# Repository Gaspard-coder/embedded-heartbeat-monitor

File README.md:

# This repository contains all of the necessary file to make a working heartbeat sensor
- Schematics
- PCB design files
- Embedded code running on MCUs

## Embedded software (`software/hsensor/`)

MicroPython application running on a Raspberry Pi Pico. It samples the
output of the TCRT5000 reflectance sensor (amplified by an op-amp), detects
heartbeats and displays the BPM together with the live waveform on the
0.96" ST7735 LCD.

### Files
- `ST7735.py` — driver for the 0.96" LCD (SPI, same wiring as the demo:
  DC=GP8, CS=GP9, SCK=GP10, MOSI=GP11, RST=GP12, BL=GP13).
- `main.py` — acquisition, heart rate detection and display loop.

### Wiring
- TCRT5000 + op-amp output → **pin 31 (GPIO26 / ADC0)** of the Pico.
- LCD: SPI1 on GP8–GP13 (see above).

### How the algorithm works

1. **Sampling.** `ADC(Pin(26))` is read every 10 ms (≈100 Hz), which is
   well above the highest expected heart-beat frequency (~3 Hz at 180 BPM)
   and matches the cutoff of the analog front-end.

2. **DC removal (high-pass filter).** The raw photoplethysmographic signal
   coming from the TCRT5000 is dominated by a large DC component (ambient
   reflectance of the skin) with a small pulsatile AC component on top. We
   subtract a slowly-tracking baseline computed as an exponential moving
   average:

   ```
   baseline ← (31 · baseline + raw) / 32
   x       ← raw − baseline
   ```

   With `α = 1/32` at 100 Hz, the equivalent cutoff is roughly 0.5 Hz —
   slow enough to leave the heartbeats untouched but fast enough to track
   drift in finger pressure or ambient light.

3. **Peak detection.** A heartbeat appears as a local maximum on the
   filtered signal `x`. For every new sample we check the *previous*
   sample: if it is greater than its two neighbours and above
   `PEAK_THRESHOLD`, it is declared a peak.

4. **Refractory period.** Once a peak has been detected, any new peak
   occurring within 300 ms is ignored. This caps the detected rate at
   200 BPM and avoids counting the dicrotic notch (the small secondary
   bump after each beat) as a separate heartbeat.

5. **BPM computation.** The time difference `dt` between two consecutive
   accepted peaks is pushed into a rolling buffer of the last 5
   intervals. The current heart rate is the average of that buffer:

   ```
   BPM = 60000 / mean(intervals_ms)
   ```

   Averaging over several beats smooths jitter due to noise and gives a
   stable reading on the display. If no peak is seen for more than 2 s
   (i.e. < 30 BPM, almost certainly a lost-contact event) the buffer is
   cleared and the BPM goes back to `--`.

6. **Display.** The LCD is refreshed every 200 ms — redrawing the full
   framebuffer is slow, so we deliberately do not refresh at the sampling
   rate. The top of the screen shows `BPM: XX`, and below it the last
   160 filtered samples are plotted (oldest on the left, newest on the
   right) with a blue zero-line.

### Tuning knobs (top of `main.py`)
- `PEAK_THRESHOLD` — minimum amplitude (in ADC LSB on the filtered signal)
  for a sample to qualify as a peak. Lower it if the analog gain is small,
  raise it if the signal is noisy.
- `BPM_WINDOW` — number of inter-beat intervals averaged.
- `REFRACTORY_MS` / `MAX_INTERVAL_MS` — accepted BPM range (currently
  30–200 BPM).
- `v // 30` in the plotting code — vertical scale of the waveform on the
  LCD.

### Running
Copy `ST7735.py` and `main.py` to the Pico (Thonny, `mpremote cp`, …).
`main.py` runs automatically at boot.

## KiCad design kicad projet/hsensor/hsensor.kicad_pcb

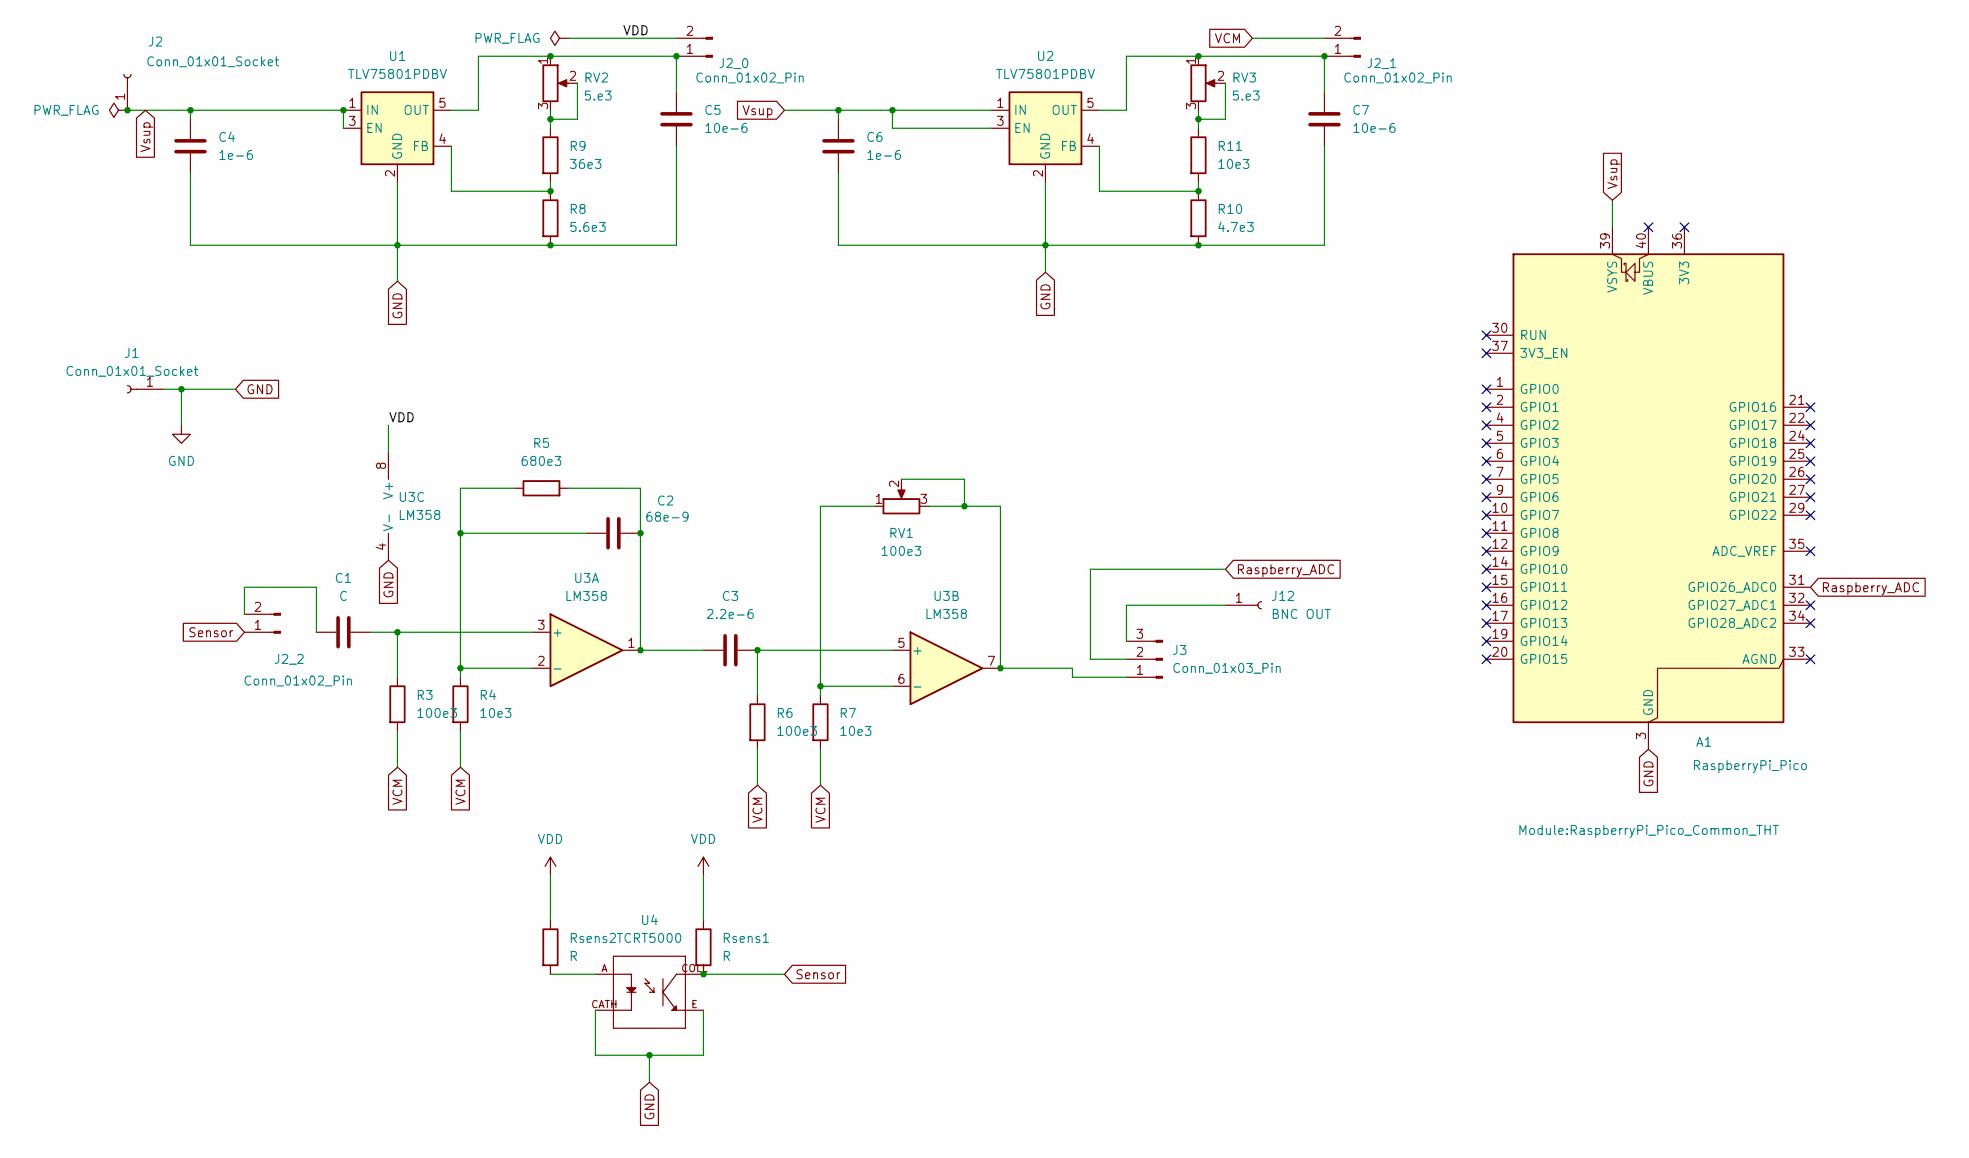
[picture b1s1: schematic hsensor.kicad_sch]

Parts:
A1: RaspberryPi_Pico; RaspberryPi_Pico_Common_THT
C1: C; C_1206_3216Metric
C2: 68e-9; C_1206_3216Metric
C3: 2.2e-6; C_1206_3216Metric
C4, C6: 1e-6; C_1206_3216Metric
C5, C7: 10e-6; C_1206_3216Metric
J1, J2: Conn_01x01_Socket
J2_0, J2_1, J2_2: Conn_01x02_Pin; PinHeader_1x02_P2.54mm_Vertical
J3: Conn_01x03_Pin; PinHeader_1x03_P2.54mm_Vertical
J12: BNC OUT
R3, R6: 100e3; R_1206_3216Metric
R4, R7, R11: 10e3; R_1206_3216Metric
R5: 680e3; R_1206_3216Metric
R8: 5.6e3; R_1206_3216Metric
R9: 36e3; R_1206_3216Metric
R10: 4.7e3; R_1206_3216Metric
RV1: 100e3; Potentiometer_Bourns_3266Y_Vertical
RV2, RV3: 5.e3; Potentiometer_Bourns_3266Y_Vertical
Rsens1, Rsens2: R; R_1206_3216Metric
U1, U2: TLV75801PDBV; SOT-23-5
U3: LM358; DIP-8_W7.62mm_Socket
U4: TCRT5000; OPTO_TCRT5000; PARTREV 1.7

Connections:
GND: A1.3 (GND), A1.8 (GND), A1.13 (GND), A1.18 (GND), A1.23 (GND), A1.28 (GND), A1.38 (GND), C4.1, C5.1, C6.1, C7.1, J1.1, R8.2, R10.2, U1.2 (GND), U2.2 (GND), U3.4 (V-), U4.CATH, U4.E
unnamed: C2.1, C3.2, R5.2, U3.1
unnamed: C5.2, J2_0.1, RV2.1, U1.5 (OUT)
unnamed: C7.2, J2_1.1, RV3.1, U2.5 (OUT)
unnamed: C1.2, J2_2.2
unnamed: J3.1, RV1.2, RV1.3, U3.7
unnamed: J3.3, J12.1
unnamed: R9.1, RV2.2, RV2.3
unnamed: R11.1, RV3.2, RV3.3
unnamed: Rsens2.2, U4.A
unnamed: R8.1, R9.2, U1.4 (FB)
unnamed: R10.1, R11.2, U2.4 (FB)
unnamed: C1.1, R3.1, U3.3 (+)
unnamed: C2.2, R4.1, R5.1, U3.2 (-)
unnamed: C3.1, R6.1, U3.5 (+)
unnamed: R7.1, RV1.1, U3.6 (-)
Raspberry_ADC: A1.31 (GPIO26_ADC0), J3.2
Sensor: J2_2.1, Rsens1.2, U4.COLL
VCM: J2_1.2, R3.2, R4.2, R6.2, R7.2
VDD: J2_0.2, Rsens1.1, Rsens2.1, U3.8 (V+)
Vsup: A1.39 (VSYS), C4.2, C6.2, J2.1, U1.1 (IN), U1.3 (EN), U2.1 (IN), U2.3 (EN)

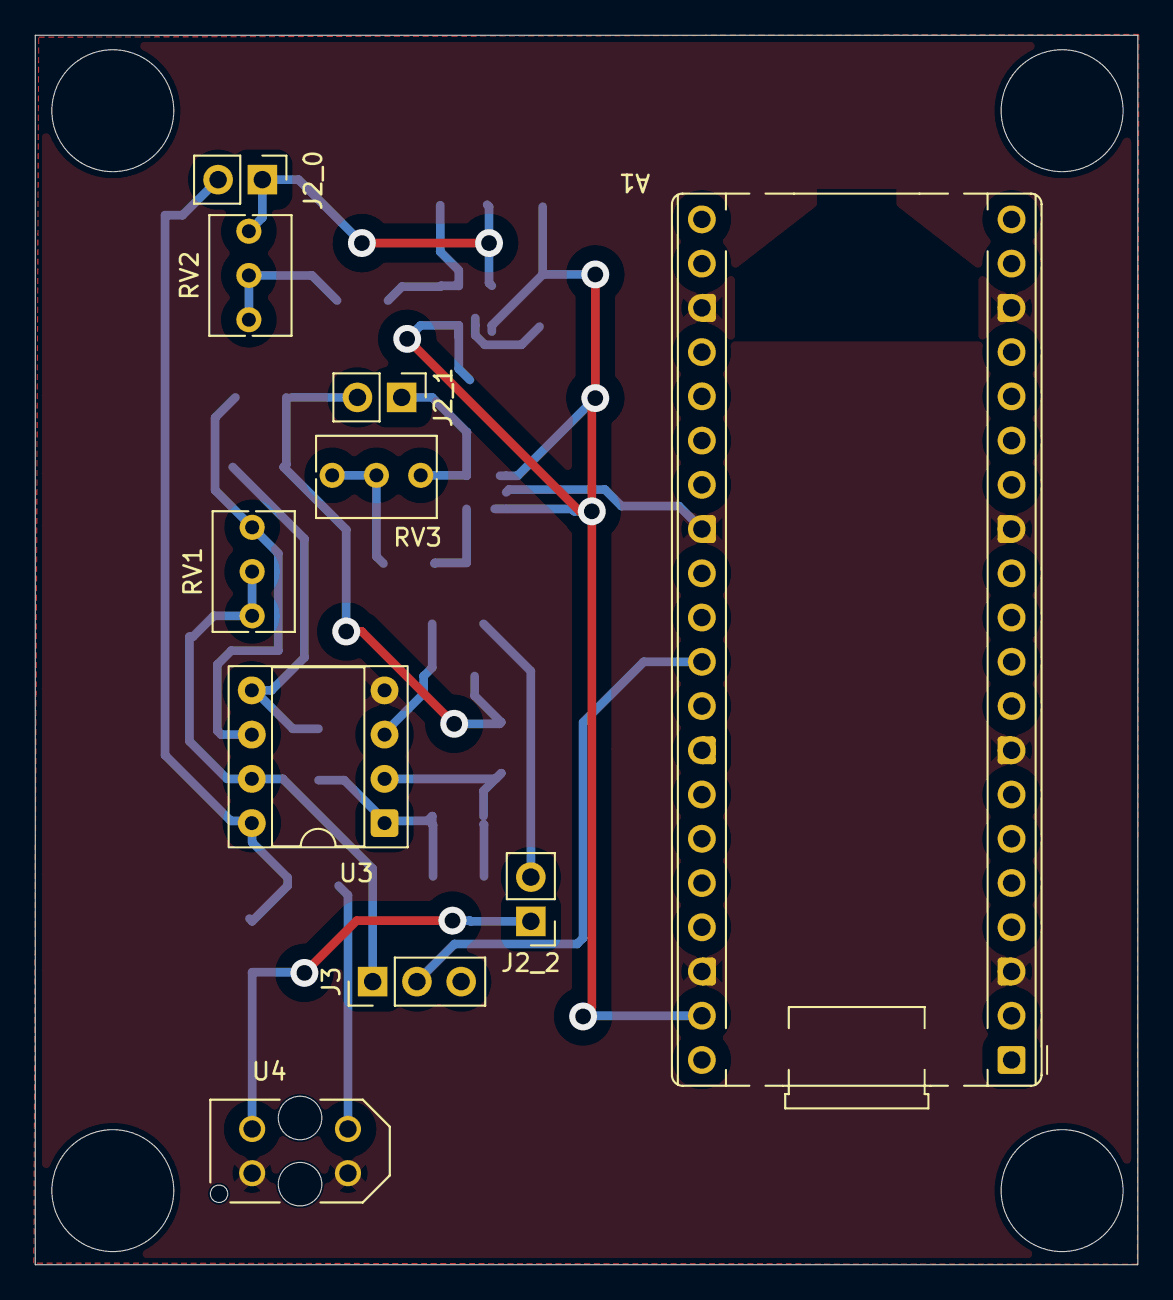
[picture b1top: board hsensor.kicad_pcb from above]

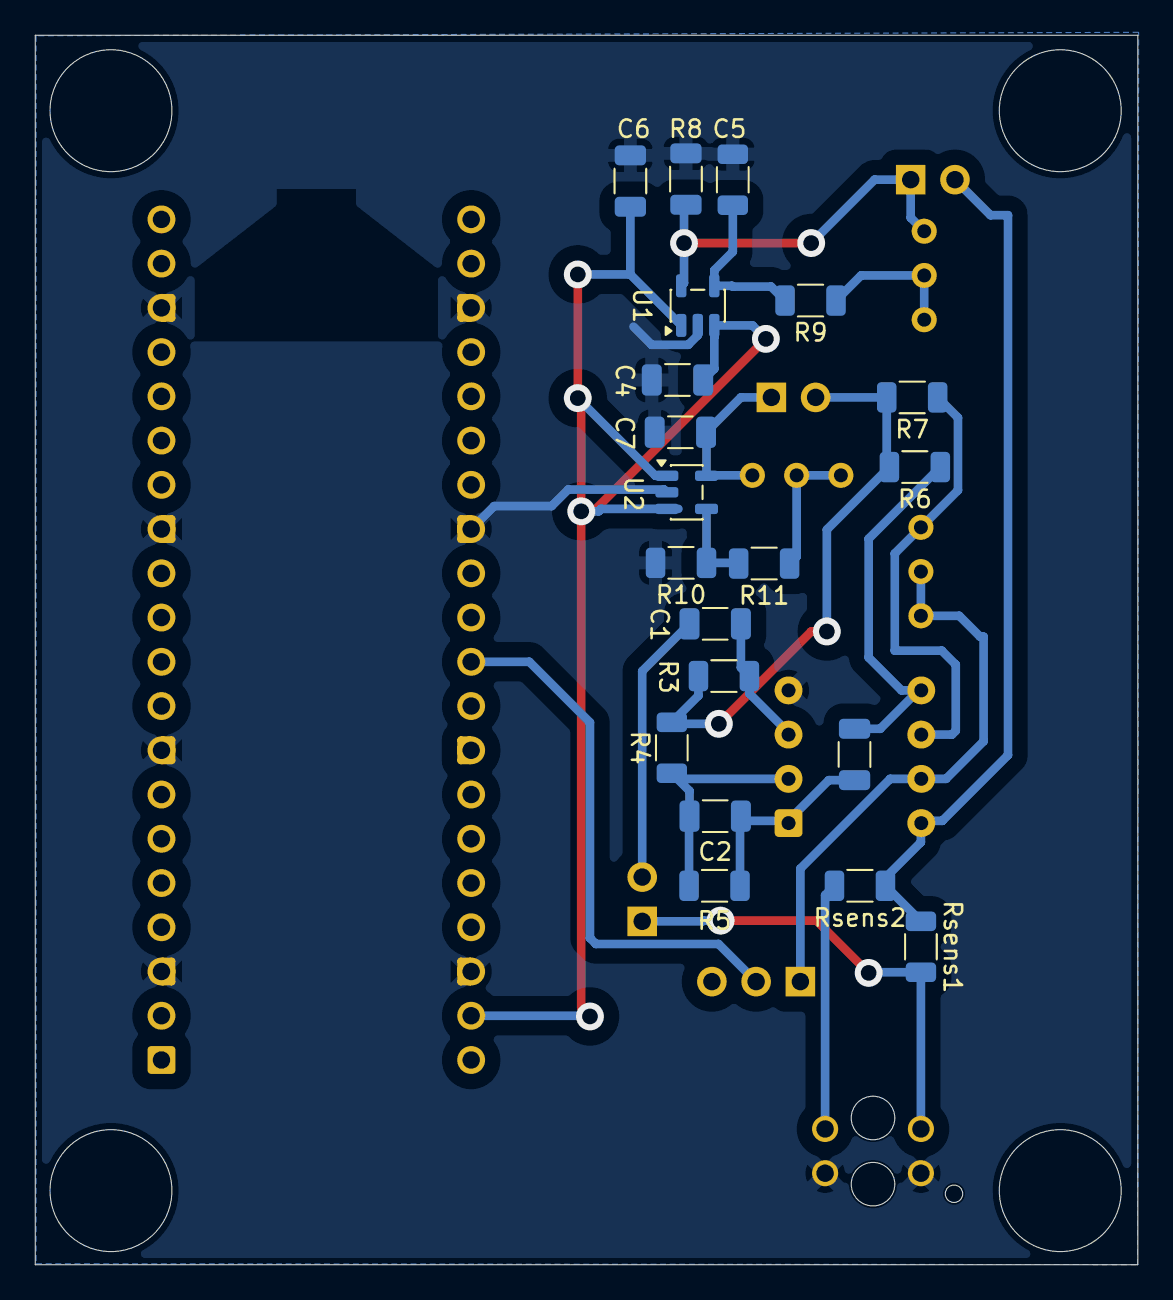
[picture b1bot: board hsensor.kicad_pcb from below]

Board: 2 copper layers, 63.3 x 70.6 mm, 30 parts (20 on the bottom side), 20 nets.

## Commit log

2026-05-20 ljkldfklj
2026-05-21 Add project overview to README.md
2026-05-23 updated schematics
2026-05-25 final pcb (i hope)
2026-06-16 added demo files
2026-06-16 added heartbeat detection software
2026-06-19 opti paramètres pour bonne mesure
